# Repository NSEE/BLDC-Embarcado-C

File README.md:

# BLDC-Embarcado-C
Acionamento e controle do BLDC embarcado em plataforma Atmel utilizando linguagem C.

## Responsável
- Cauê Menegaldo

## Organização das Pastas
As pastas desse projeto estão organizadas conforme padrao_pastas-nsee:

Árvore de arquivos :
```
├── Como
│   ├── Apresentações
│   ├── Datasheets
│   ├── Estudos
│   ├── Manuais
│   ├── Referências
│   │   └── Artigos
│   │       └── Bibliografia
│   └── Wiki
├── Materiais
│   ├── Arquivos
│   │   └── Orçamentos
│   ├── Códigos
│   │   └── Atmel
│   ├── Fotos
│   └── PCB

```

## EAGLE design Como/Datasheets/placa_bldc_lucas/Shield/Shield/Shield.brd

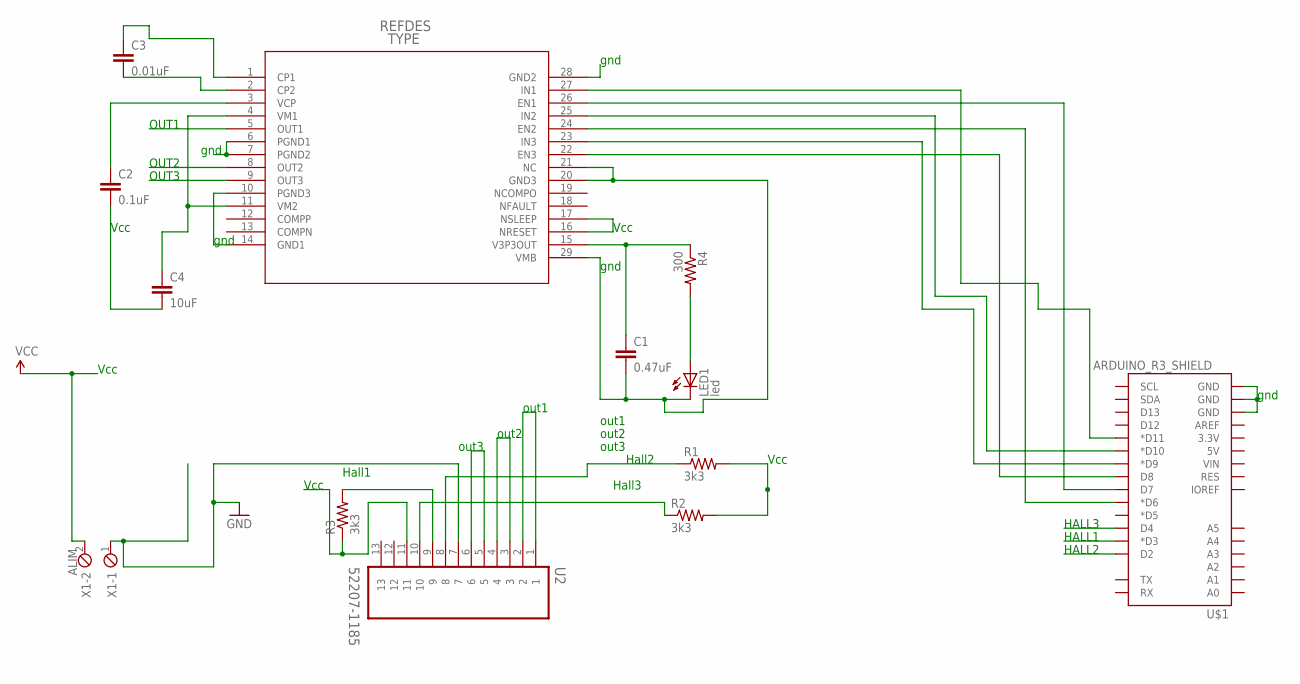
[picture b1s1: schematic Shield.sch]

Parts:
C1: 0.47uF; C025-025X050
C2: 0.1uF; C102-043X133
C3: 0.01uF; C025-025X050
C4: 10uF; C025-050X050
LED1: led; LED3MM
R1, R2, R3: 3k3; 0207/10
R4: 300; 0207/10
U1: DRV8811_PWP_28; PWP28_5P18X3P1
U2: 52207-1185; MOLEX_52207-1185
U$1: ARDUINO_R3_SHIELD; UNO_R3_SHIELD
X1: ALIM; 2POL254

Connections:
GND: C1.2, LED1.K (C), U1.6 (PGND1), U1.7 (PGND2), U1.10 (PGND3), U1.14 (GND1), U1.20 (GND3), U1.21 (NC), U1.28 (GND2), U1.29 (VMB), U2.7, U$1.GND@0 (GND), U$1.GND@1 (GND), U$1.GND@2 (GND), X1.1
HALL1: R3.2, U2.9, U$1.D3 (*D3)
HALL2: R1.1, U2.8, U$1.D2
HALL3: R2.1, U2.10, U$1.D4
unnamed: U1.27 (IN1), U$1.D11 (*D11)
unnamed: U1.26 (EN1), U$1.D7
unnamed: U1.24 (EN2), U$1.D6 (*D6)
unnamed: U1.25 (IN2), U$1.D10 (*D10)
unnamed: U1.23 (IN3), U$1.D9 (*D9)
unnamed: U1.22 (EN3), U$1.D8
unnamed: LED1.A, R4.2
unnamed: C1.1, R4.1, U1.15 (V3P3OUT)
unnamed: C2.1, U1.3 (VCP)
unnamed: C3.2, U1.2 (CP2)
unnamed: C3.1, U1.1 (CP1)
unnamed: C4.1, U1.4 (VM1), U1.11 (VM2)
OUT1: U1.5 (OUT1), U2.1, U2.2
OUT2: U1.8 (OUT2), U2.3, U2.4
OUT3: U1.9 (OUT3), U2.5, U2.6
VCC: C2.2, C4.2, R1.2, R2.2, R3.1, U1.16 (NRESET), U1.17 (NSLEEP), U2.11, X1.2

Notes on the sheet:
Vcc
out3
out2
out1
Hall2
Hall3
Hall1
gnd
OUT1
OUT2
OUT3
HALL1
HALL2
HALL3

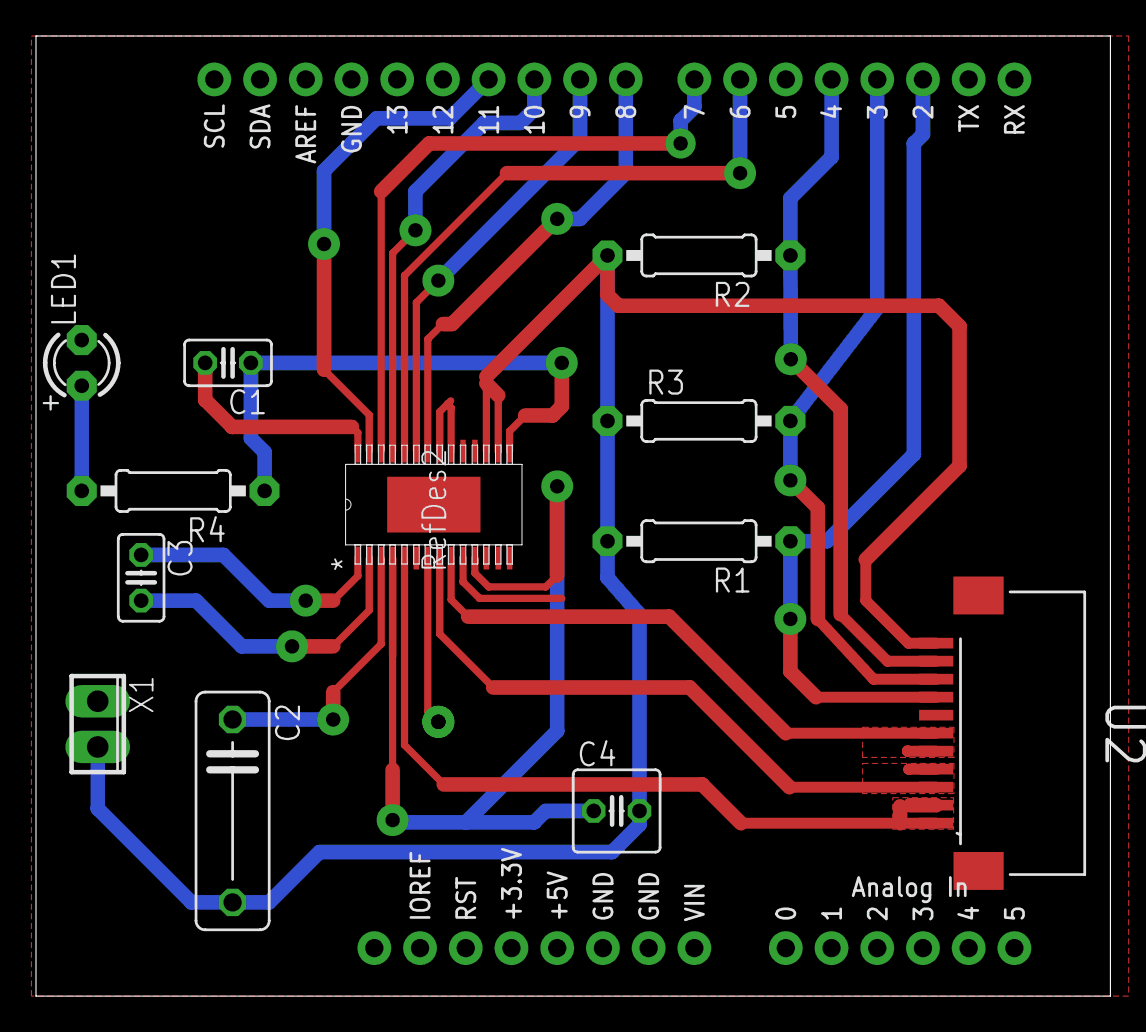
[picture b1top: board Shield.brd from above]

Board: 2 copper layers, 59.7 x 53.3 mm, 13 parts (0 on the bottom side), 20 nets.

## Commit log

2015-05-13 Organizando arquivos no git
2015-05-13 organizando .gitignore para arquivos .c
2015-05-13 six-step: leitura do hall e definicao das fases de acionamento
2015-05-13 utilizando pwm para acionar os leds da placa.
2015-05-15 Datasheet de acionamento em blocos da maxon
2015-05-15 Organizando a estrutura do codigo.
2015-05-15 PWM alinhado a esqueda e comeca em baixa
2015-05-19 PWM e enable em tres saidas distintas, falta teste pratico.
2015-05-21 Metodo six-step funcioando em um sentido.
2015-05-22 Add rotina para iniciar o acionamento automatico.
2015-05-22 Add escolha do sentido de rotacao do motor.
2015-06-02 Tentativa falha de incluir TC
2015-06-02 Revert "Add escolha do sentido de rotacao do motor."
    This reverts commit 24cb2e5c43b6b7f508213a546e6279a84162ebde.
2015-06-02 Revert "Tentativa falha de incluir TC"
    This reverts commit 01526c564d85e66a23c198614a639c34dbbac25d.
2015-06-02 placa de potencia .pdf
2015-06-02 Acionamento six-step dois sentidos funcionando.
2015-06-03 Medindo velocidade pulso/tempo fixo
2015-06-23 Corrigindo medida de velocidade
    Atentar para a quantidade de polos e também o fato de o hall acionar em
    borda de subida e descida, sendo necessario dividir por 2.
2015-06-23 Variando o pwm em 0,1%
2015-06-24 Inicia o duty_cicle em 30 para facilitar o teste.
2015-06-26 aumenta em 10% o duty_cicle a cada 500ms
2015-06-29 Automatização do teste de zona morta.
    Inicia o duty cicle do pwm em 30% e a cada 750ms incremente em 1%
    (0,12V) parando de incrementar assim que o motor começa a girar.
2015-07-01 Mostrar pwm para analise.
2015-07-02 Alteração da frequencia do pwm para 20kHz
2015-09-09 anotacoes sobre pid
    Anotações gerais sobre PID, discretização e implementação digital.
2015-09-09 frequencia do pwm alterada para 20kHz
2015-09-14 Finalizando conteúdo.
2015-09-14 Melhorando os comentários do código.
2015-10-05 Organizacao
2015-10-08 testando
2015-10-21 evolucao
2015-10-21 Corrigindo bug - Funcionando ok - verificar conexoes
2015-10-22 Inclusão de comunicação serial para leitura e escrita - funcionando.
2015-10-22 Organizacao do main.c
2015-11-04 Acionamento funcioando. Aterior a implementacao do touch.
2015-11-06 Atualizacao e melhorias.
2015-11-06 implementacao do touch
2015-11-06 Implementacao do qtouch com sucesso.
2015-11-06 melhorias.
2015-11-09 Atualizacao
2015-11-09 Corrigindo problema de iniciar o motor.
2015-11-10 Atualizacao e correcao de bugs.
2016-02-16 Atualizacao e organizacao
2016-03-23 projet genius pic18f funcionando
2016-03-23 comentado codigo
2016-03-30 Documento padrão init.c
2016-03-30 Revert "Documento padrão init.c"
    This reverts commit d4a83fa2dc2c6edcbf9ec147eb023d06344f297c.
2016-03-30 Documentos Padrão da Microchip
2016-03-30 modelo CLOSEDLOOP
2016-03-30 Solução problema do Potenciômetro
    Na programação foi retirado o #define do Closed Loop, portanto rodando
    programa inteiro em malha aberta.
    Em malha aberta o motor pegava corretamente o valor do potenciometro e
    variava conforme o mesmo.
2016-03-31 Organização documentos padrão
    Todos os documentos sao padrão da Microchip
2016-04-04 Códigos do AN957
    Mudanças e criação de funções nos códigos do AN957 para inicializar a
    UART, rodar o motor variando com a potência também em Closed Loop.
2016-04-04 Função de inicialização da UART
2016-04-07 Uso da Uart e Maior potencia para o motor
    Foram colocadas funcoes para aparecer a velocidade instantanea domotor e
    o erro entre a velocidade do motor e a velocidade exigida pelo
    potenciometro.
    Tambem foi aumentada a constante multiplicadora (POTMULT) para o que
    seria o valor maximo de 8, por causa de cálculos visando a velocidade
    maxima que o motor podeira chegar segundo seu Datasheet.
2016-04-26 UART open e closed, Baud Rate, Duty cycle
    -Aumento do Baud Rate da UART de 9600 para 56000.
    -Ativação do High Speed Mode da UART. (4 clocks por period de bit)
    -UART no Closed Loop: informa o valor do potenciometro em hexadecimal,
    velocidade do motor (em RPM) e o set-point (em RPM).
    -UART no Open Loop: informa valor do potenciometro em hexa, velocidade
    do motor (em RPM) e o o duty-cycle do PWM (em %), calculado por meio de

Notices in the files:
parts and their libraries:
SparkFun-Boards: Licensing: Creative Commons ShareAlike 4.0 International - https://creativecommons.org/licenses/by-sa/4.0
SparkFun: Licensing: CC v3.0 Share-Alike You are welcome to use this library for commercial purposes.
